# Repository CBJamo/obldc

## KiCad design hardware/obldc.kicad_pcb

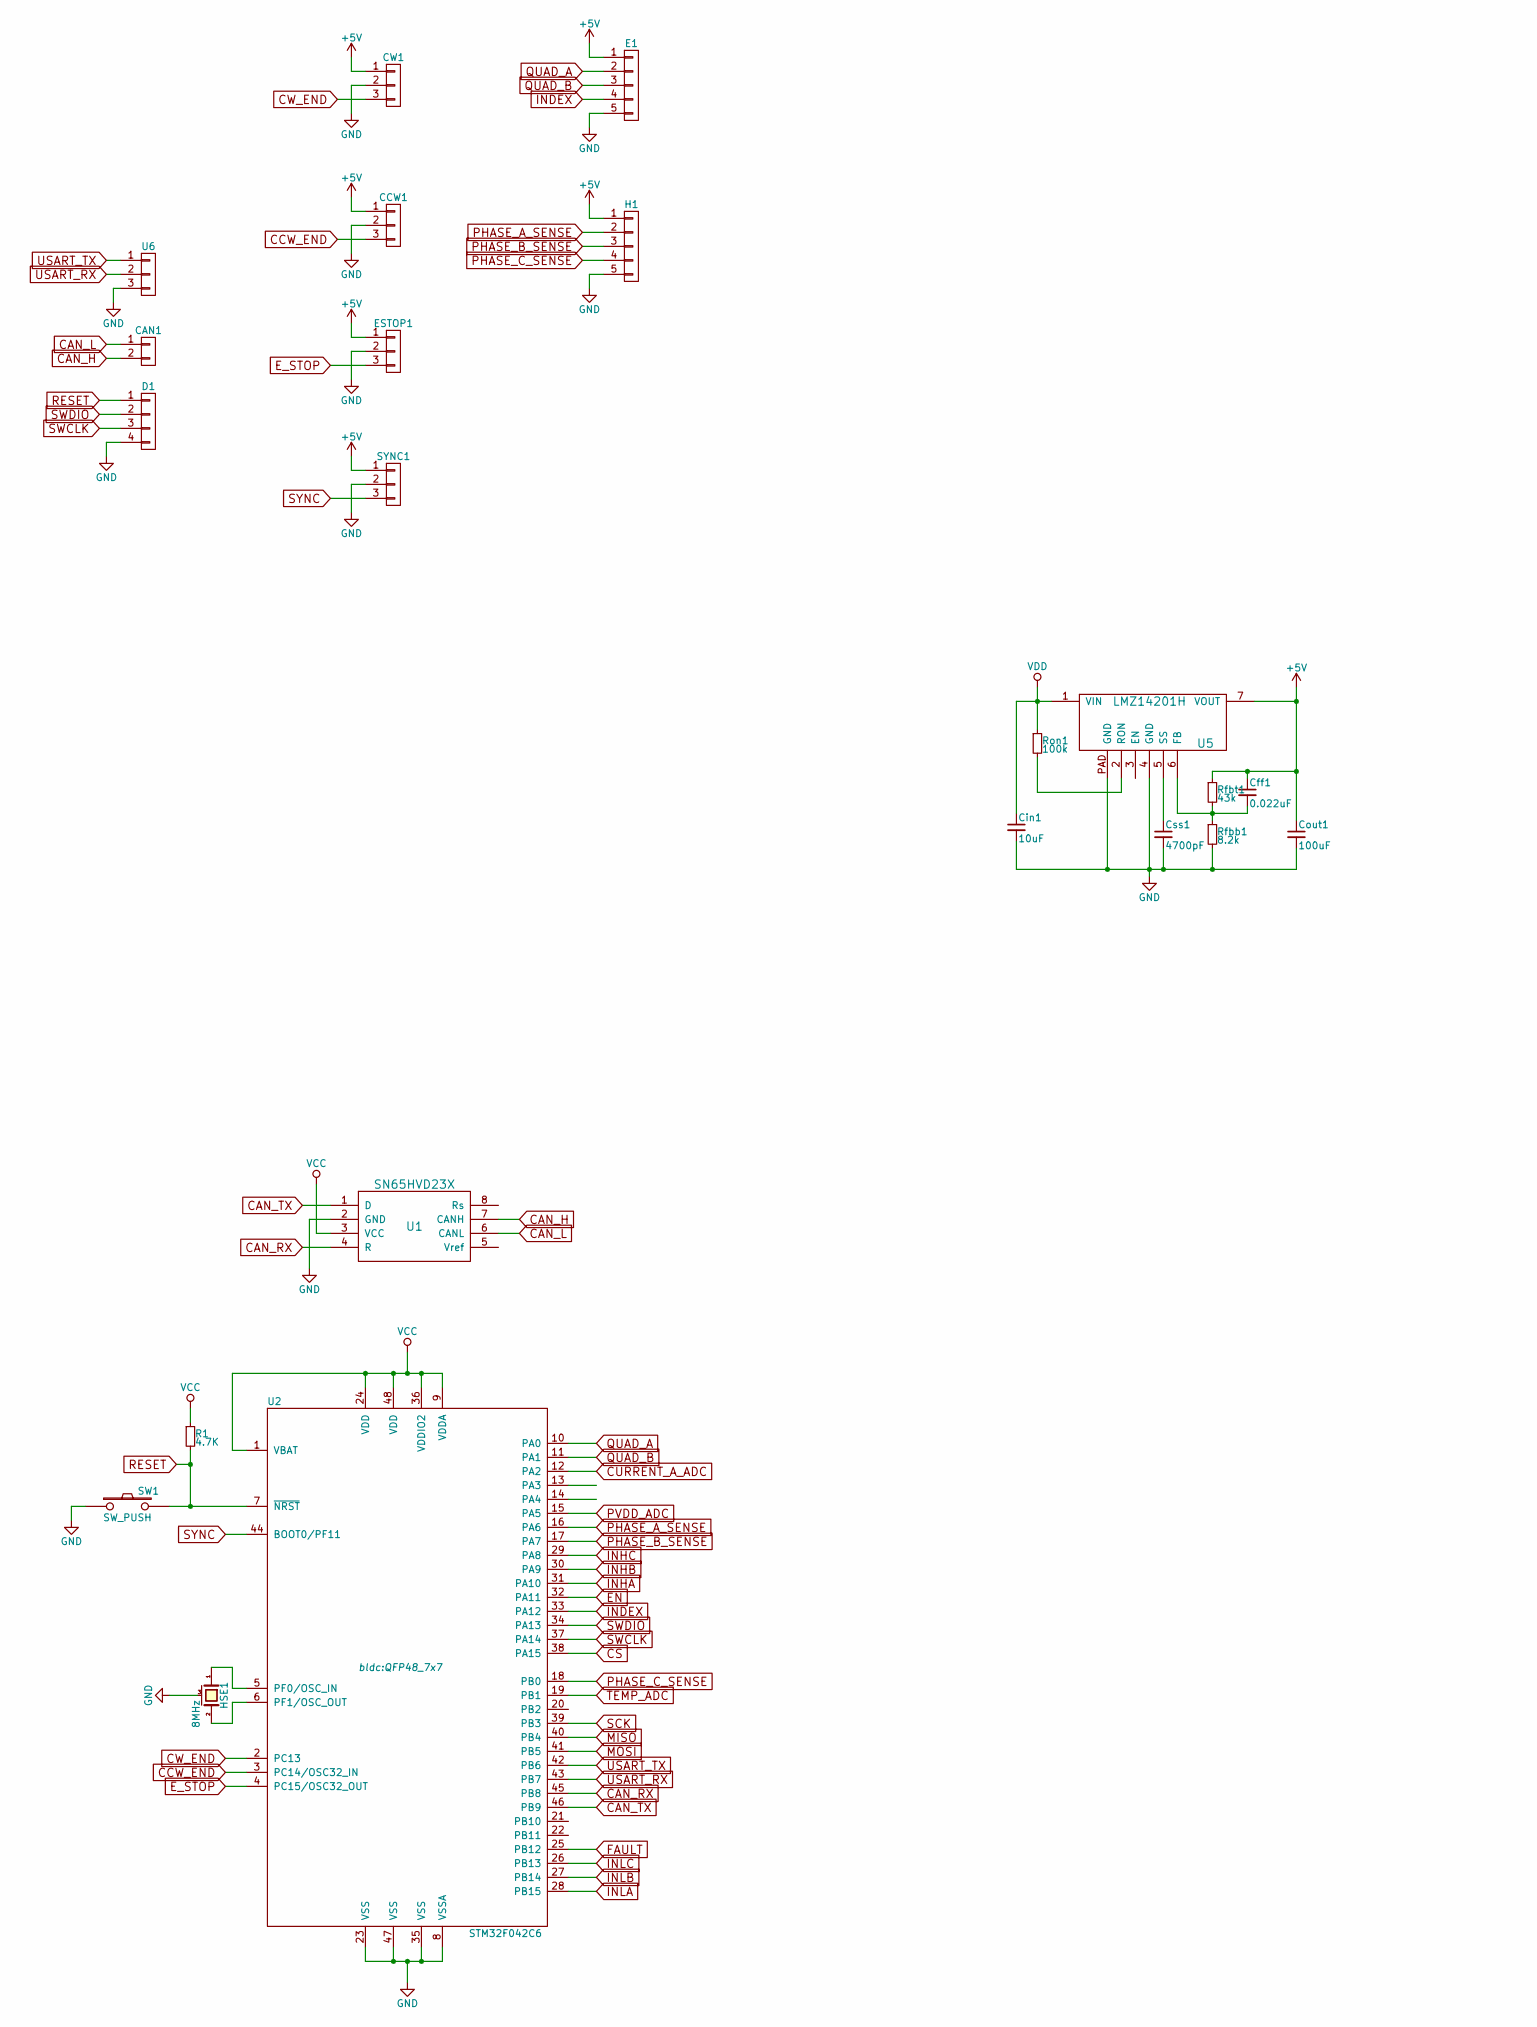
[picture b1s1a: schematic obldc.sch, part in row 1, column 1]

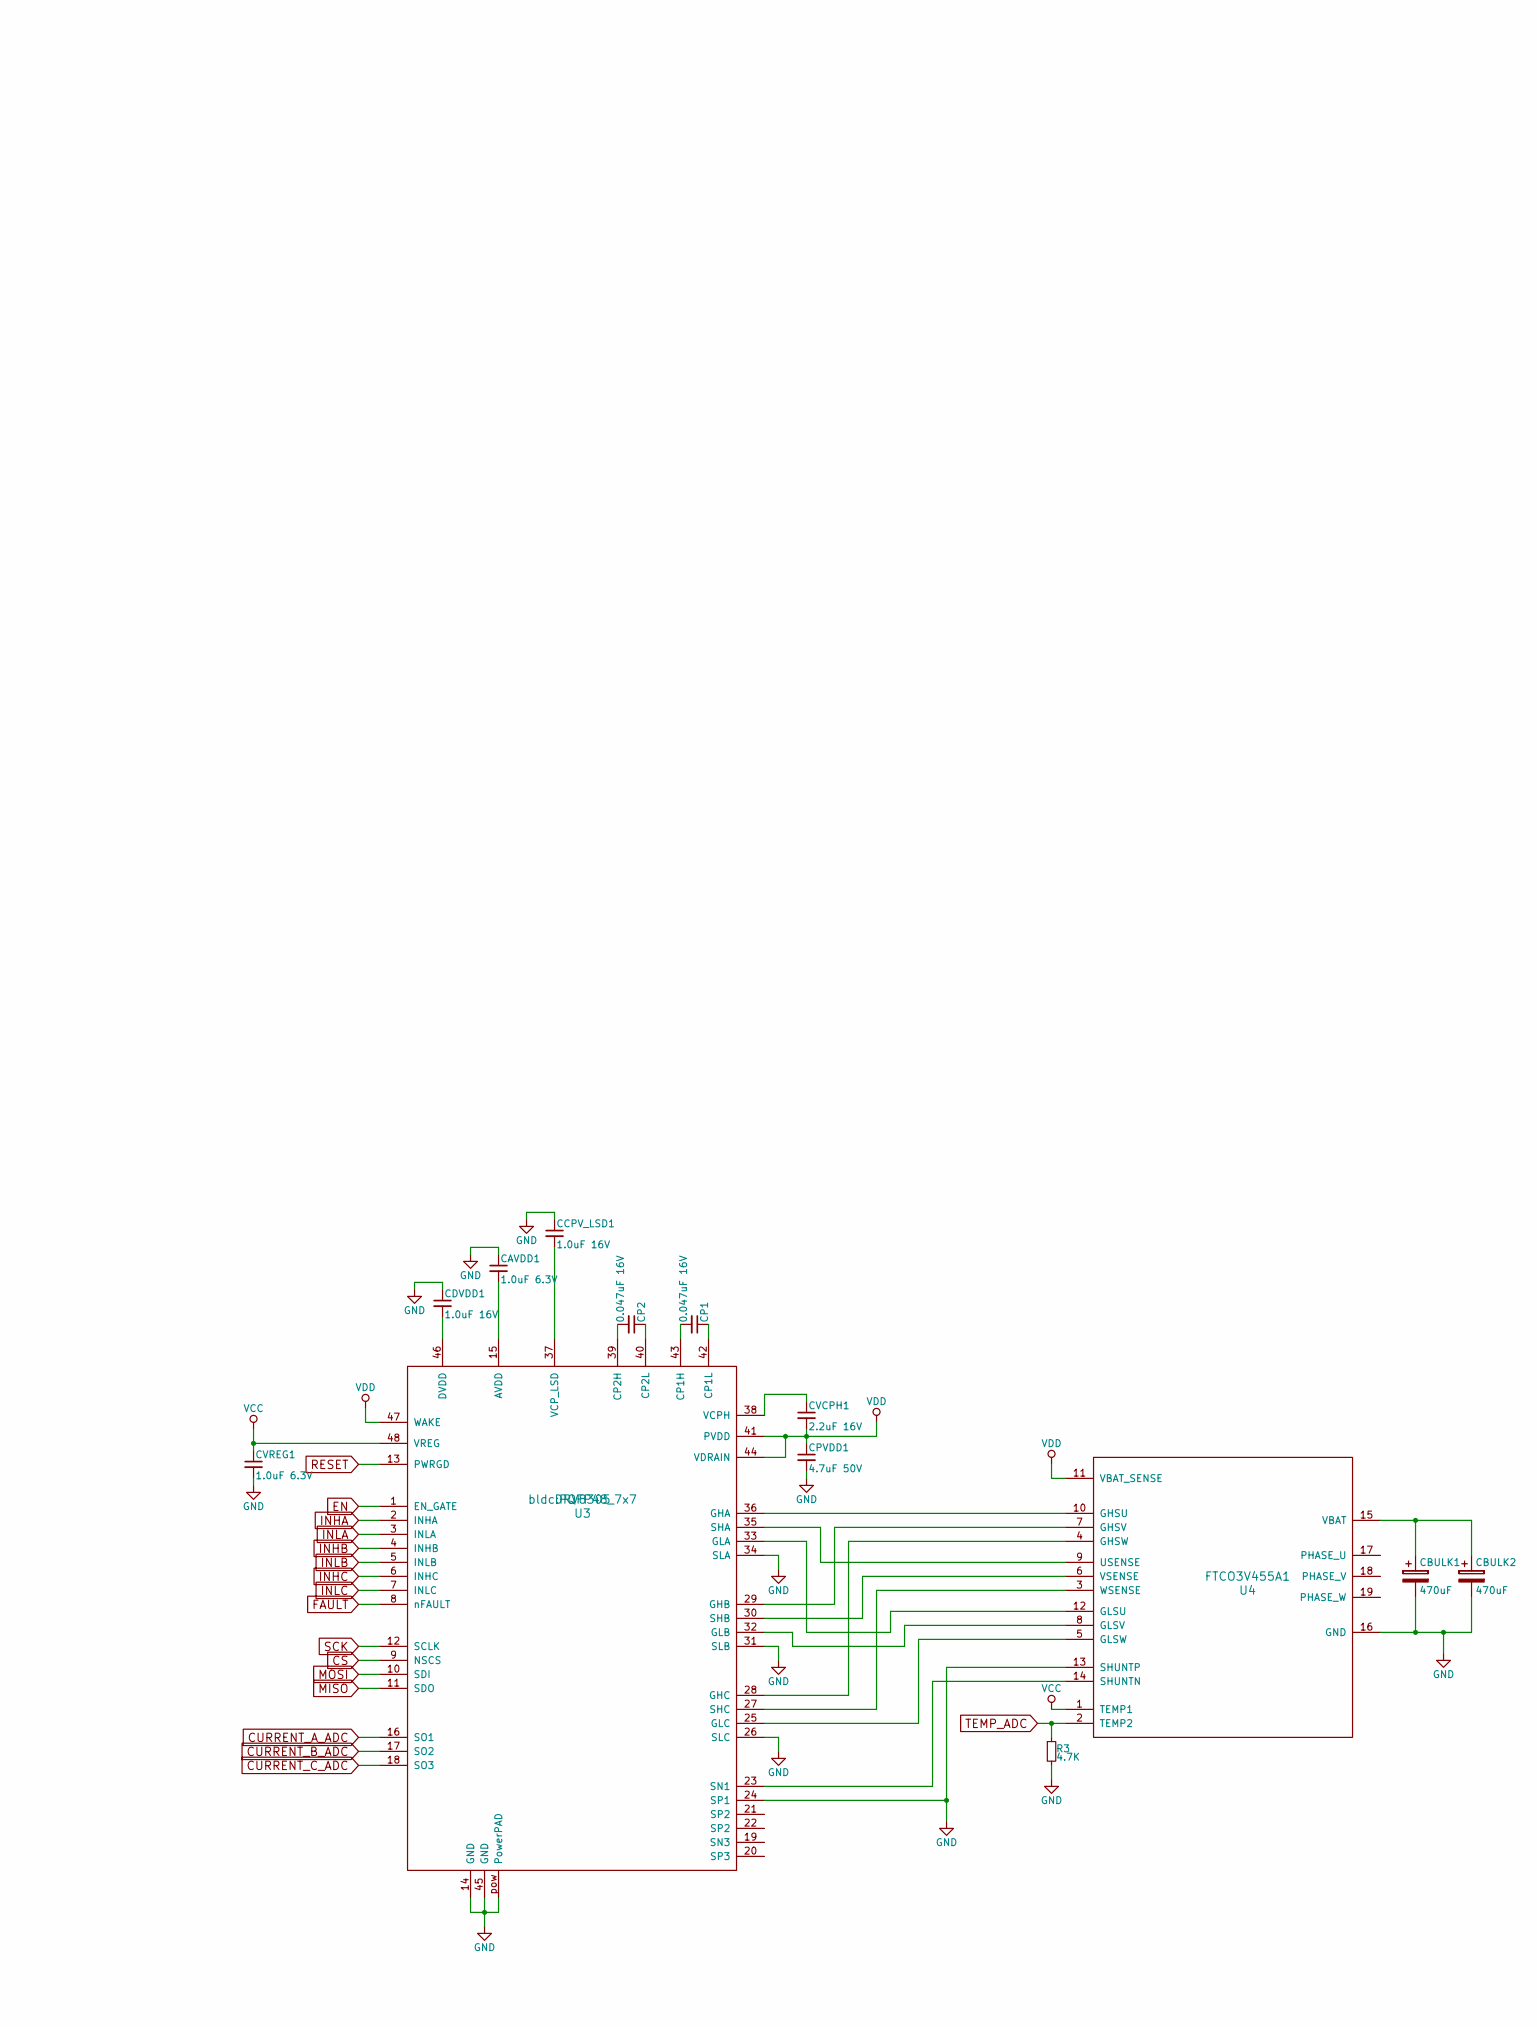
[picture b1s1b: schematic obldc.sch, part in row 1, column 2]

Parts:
CAN1: Pin_Header_Straight_1x02
CAVDD1: 1.0uF 6.3V; C_0402
CBULK1, CBULK2: 470uF; C_Radial_D12.5_L25_P5
CCPV_LSD1: 1.0uF 16V; C_0402
CCW1: Pin_Header_Straight_1x03
CDVDD1: 1.0uF 16V; C_0402
CP1, CP2: 0.047uF 16V; C_0402
CPVDD1: 4.7uF 50V; C_1206
CVCPH1: 2.2uF 16V; C_1206
CVREG1: 1.0uF 6.3V; C_0402
CW1: Pin_Header_Straight_1x03
Cff1: 0.022uF; C_0402
Cin1: 10uF; C_1206
Cout1: 100uF; C_1206
Css1: 4700pF; C_0402
D1: Pin_Header_Straight_1x04
E1: Pin_Header_Straight_1x05
ESTOP1: Pin_Header_Straight_1x03
H1: Pin_Header_Straight_1x05
HSE1: 8MHz; CSTCE_V13C
R1, R3: 4.7K; R_0402
Rfbb1: 8.2k; R_0402
Rfbt1: 43k; R_0402
Ron1: 100k; R_0402
SW1: SW_PUSH; SW_SPST_FSMSM
SYNC1: Pin_Header_Straight_1x03
U1: SN65HVD23X; SOIJ-8_5.3x5.3mm_Pitch1.27mm
U2: STM32F042C6; QFP48_7x7
U3: DRV8305; PQFP48_7x7
U4: FTCO3V455A1
U5: LMZ14201H; NDW0007A
U6: Pin_Header_Straight_1x03

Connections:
+5V: CCW1.1, CW1.1, Cff1.1, Cout1.1, E1.1, ESTOP1.1, H1.1, Rfbt1.1, SYNC1.1, U5.7 (VOUT)
CAN_H: CAN1.2, U1.7 (CANH)
CAN_L: CAN1.1, U1.6 (CANL)
CAN_RX: U1.4 (R), U2.45 (PB8)
CAN_TX: U1.1 (D), U2.46 (PB9)
CCW_END: CCW1.3, U2.3 (PC14/OSC32_IN)
CS: U2.38 (PA15), U3.9 (NSCS)
CURRENT_A_ADC: U2.12 (PA2), U3.16 (SO1)
CURRENT_B_ADC: U3.17 (SO2)
CURRENT_C_ADC: U3.18 (SO3)
CW_END: CW1.3, U2.2 (PC13)
EN: U2.32 (PA11), U3.1 (EN_GATE)
E_STOP: ESTOP1.3, U2.4 (PC15/OSC32_OUT)
FAULT: U2.25 (PB12), U3.8 (nFAULT)
GND: CAVDD1.1, CBULK1.2, CBULK2.2, CCPV_LSD1.1, CCW1.2, CDVDD1.1, CPVDD1.2, CVREG1.2, CW1.2, Cin1.2, Cout1.2, Css1.2, D1.4, E1.5, ESTOP1.2, H1.5, HSE1.3 (case), R3.2, Rfbb1.2, SW1.1, SYNC1.2, U1.2 (GND), U2.8 (VSSA), U2.23 (VSS), U2.35 (VSS), U2.47 (VSS), U3.14 (GND), U3.24 (SP1), U3.26 (SLC), U3.31 (SLB), U3.34 (SLA), U3.45 (GND), U3.pow (PowerPAD), U4.13 (SHUNTP), U4.16 (GND), U5.4 (GND), U5.PAD (GND), U6.3
INDEX: E1.4, U2.33 (PA12)
INHA: U2.31 (PA10), U3.2 (INHA)
INHB: U2.30 (PA9), U3.4 (INHB)
INHC: U2.29 (PA8), U3.6 (INHC)
INLA: U2.28 (PB15), U3.3 (INLA)
INLB: U2.27 (PB14), U3.5 (INLB)
INLC: U2.26 (PB13), U3.7 (INLC)
MISO: U2.40 (PB4), U3.11 (SDO)
MOSI: U2.41 (PB5), U3.10 (SDI)
unnamed: CAVDD1.2, U3.15 (AVDD)
unnamed: CBULK1.1, CBULK2.1, U4.15 (VBAT)
unnamed: CCPV_LSD1.2, U3.37 (VCP_LSD)
unnamed: CDVDD1.2, U3.46 (DVDD)
unnamed: CP1.1, U3.42 (CP1L)
unnamed: CP1.2, U3.43 (CP1H)
unnamed: CP2.1, U3.40 (CP2L)
unnamed: CP2.2, U3.39 (CP2H)
unnamed: CVCPH1.1, U3.38 (VCPH)
unnamed: Cff1.2, Rfbb1.1, Rfbt1.2, U5.6 (FB)
unnamed: Css1.1, U5.5 (SS)
unnamed: HSE1.1, U2.5 (PF0/OSC_IN)
unnamed: HSE1.2, U2.6 (PF1/OSC_OUT)
unnamed: Ron1.2, U5.2 (RON)
unnamed: U3.23 (SN1), U4.14 (SHUNTN)
unnamed: U3.25 (GLC), U4.5 (GLSW)
unnamed: U3.27 (SHC), U4.3 (WSENSE)
unnamed: U3.28 (GHC), U4.4 (GHSW)
unnamed: U3.29 (GHB), U4.7 (GHSV)
unnamed: U3.30 (SHB), U4.6 (VSENSE)
unnamed: U3.32 (GLB), U4.8 (GLSV)
unnamed: U3.33 (GLA), U4.12 (GLSU)
unnamed: U3.35 (SHA), U4.9 (USENSE)
unnamed: U3.36 (GHA), U4.10 (GHSU)
PHASE_A_SENSE: H1.2, U2.16 (PA6)
PHASE_B_SENSE: H1.3, U2.17 (PA7)
PHASE_C_SENSE: H1.4, U2.18 (PB0)
PVDD_ADC: U2.15 (PA5)
QUAD_A: E1.2, U2.10 (PA0)
QUAD_B: E1.3, U2.11 (PA1)
RESET: D1.1, R1.2, SW1.2, U2.7 (~NRST), U3.13 (PWRGD)
SCK: U2.39 (PB3), U3.12 (SCLK)
SWCLK: D1.3, U2.37 (PA14)
SWDIO: D1.2, U2.34 (PA13)
SYNC: SYNC1.3, U2.44 (BOOT0/PF11)
TEMP_ADC: R3.1, U2.19 (PB1), U4.2 (TEMP2)
USART_RX: U2.43 (PB7), U6.2
USART_TX: U2.42 (PB6), U6.1
VCC: CVREG1.1, R1.1, U1.3 (VCC), U2.1 (VBAT), U2.9 (VDDA), U2.24 (VDD), U2.36 (VDDIO2), U2.48 (VDD), U3.48 (VREG), U4.1 (TEMP1)
VDD: CPVDD1.1, CVCPH1.2, Cin1.1, Ron1.1, U3.41 (PVDD), U3.44 (VDRAIN), U3.47 (WAKE), U4.11 (VBAT_SENSE), U5.1 (VIN)

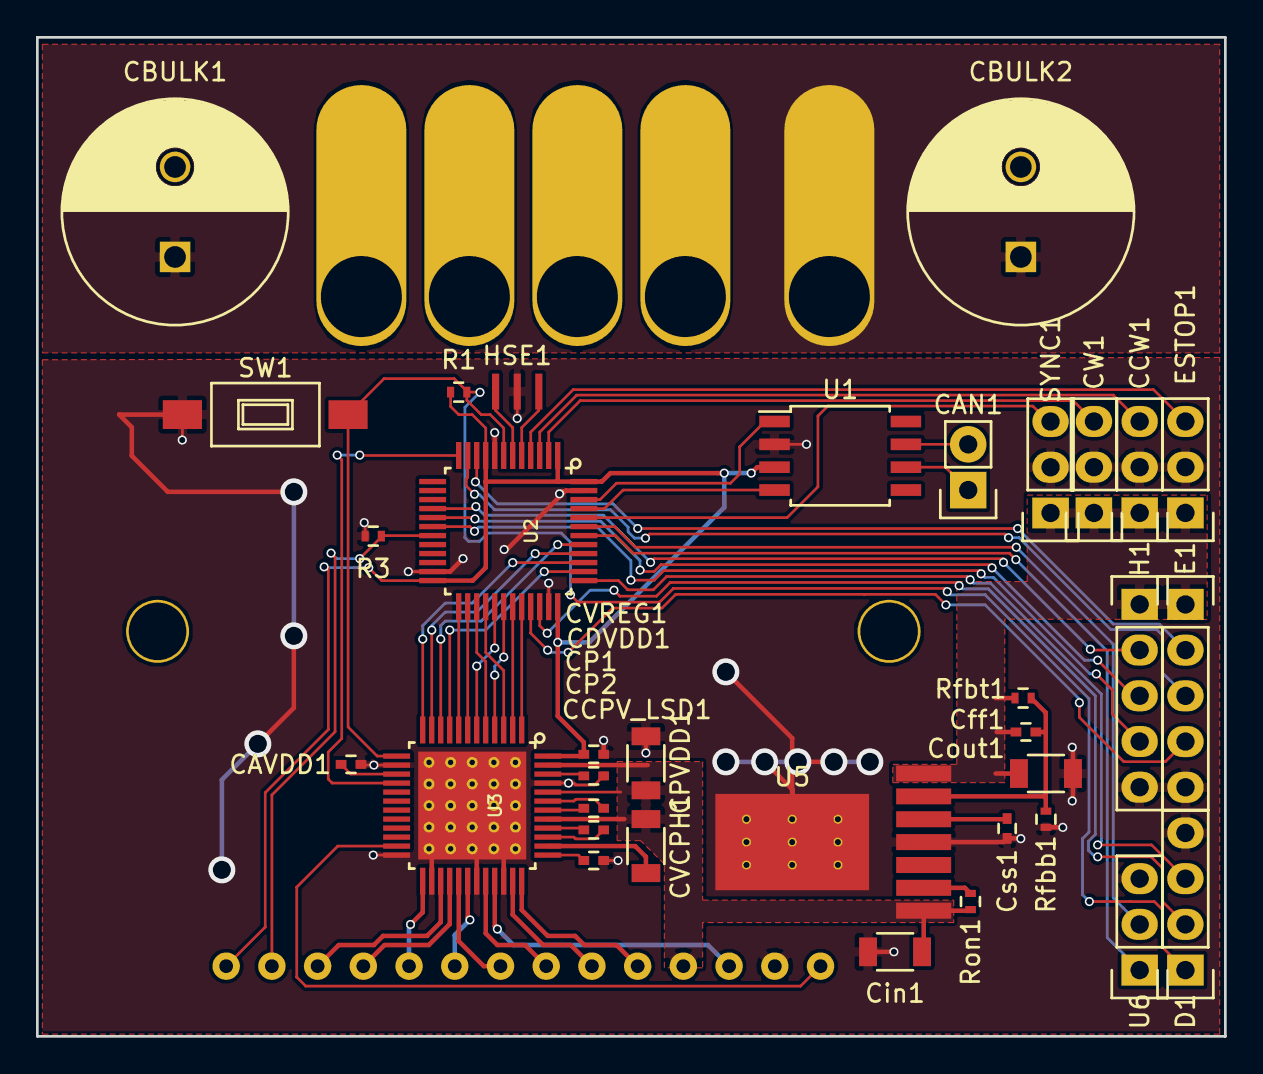
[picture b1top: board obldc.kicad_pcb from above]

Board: 2 copper layers, 66.0 x 55.5 mm, 35 parts (1 on the bottom side), 61 nets.

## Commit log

2016-03-03 Inital commit
2016-05-01 Changed ldscripts for stm32f04xx
2016-05-01 Misc admin files
2016-05-01 .gitignore update
2016-05-01 Use external crystal
2016-05-01 Major src update
2016-05-01 Docs
